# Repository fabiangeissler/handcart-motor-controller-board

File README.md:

# handcart-motor-controller-board
High Power (24V, >1kW) motor controller board for use in electric handcart. Communication via RS-485 bus.

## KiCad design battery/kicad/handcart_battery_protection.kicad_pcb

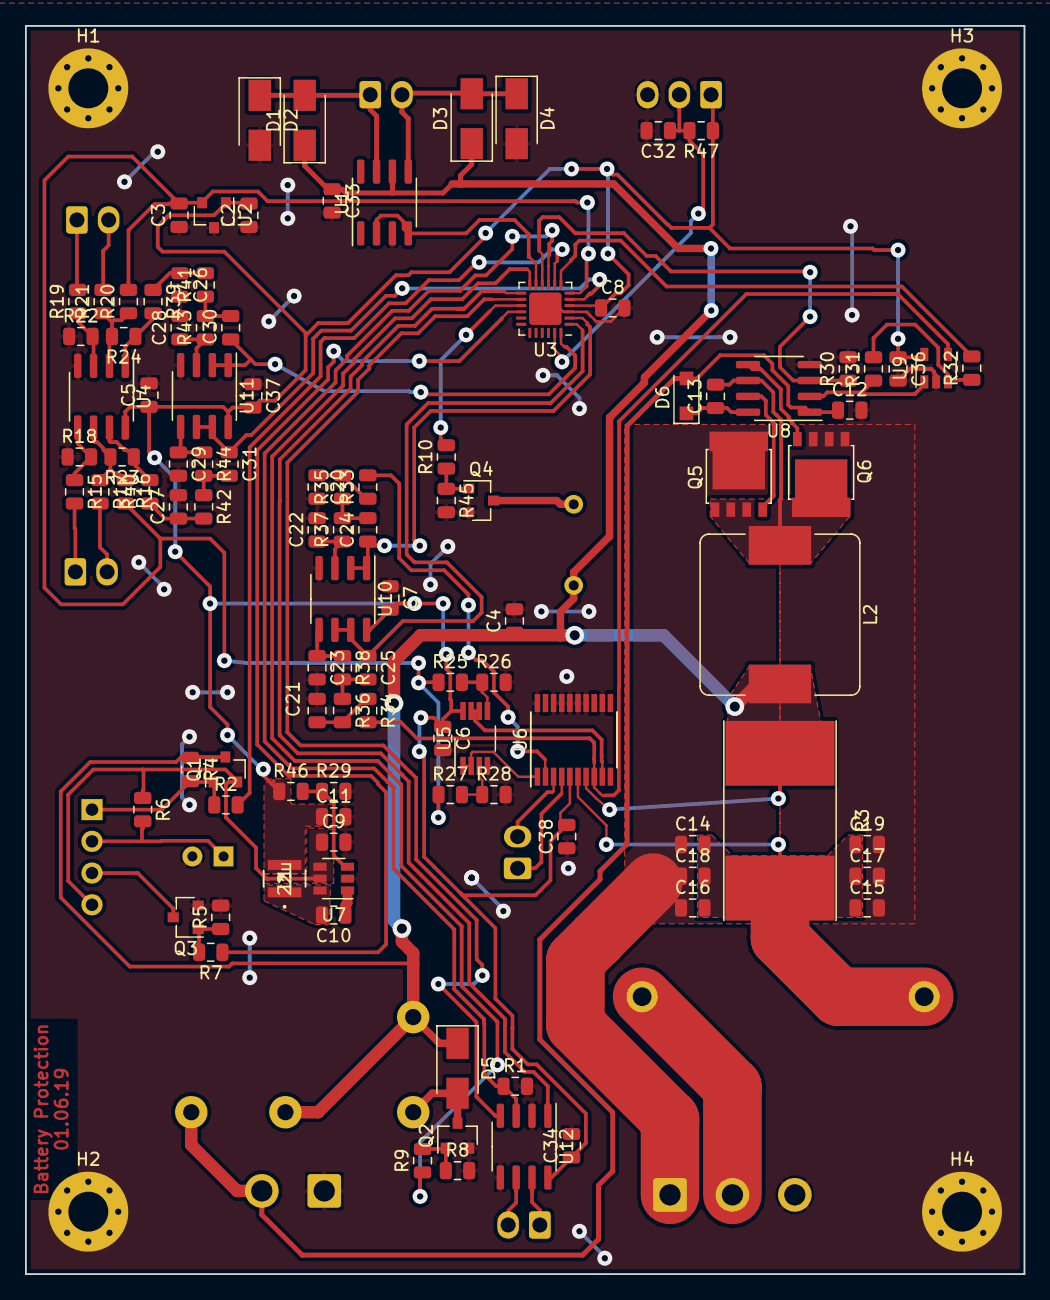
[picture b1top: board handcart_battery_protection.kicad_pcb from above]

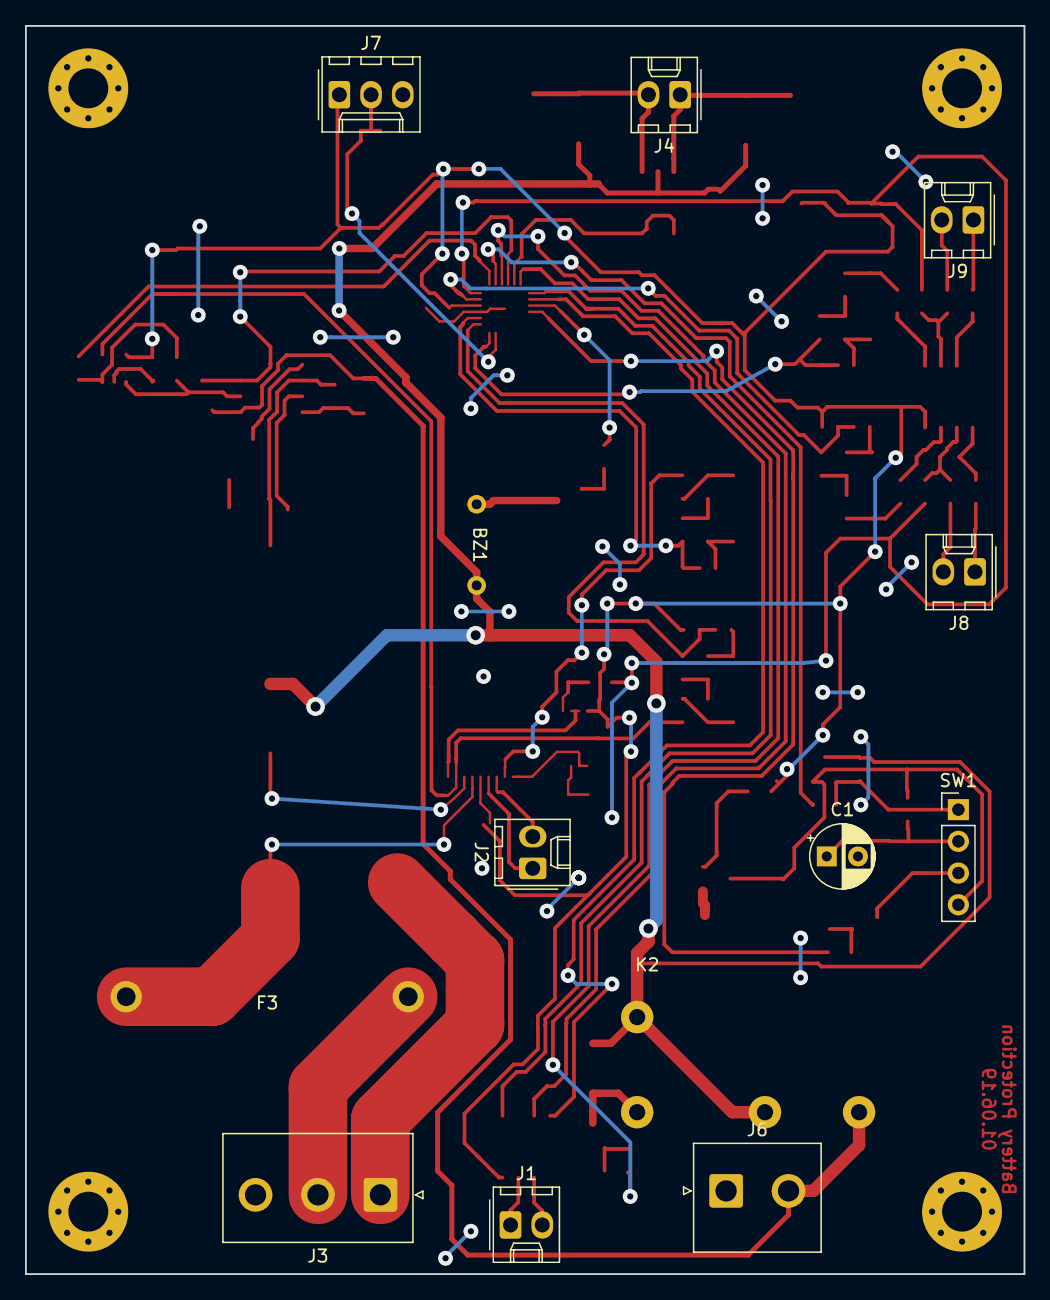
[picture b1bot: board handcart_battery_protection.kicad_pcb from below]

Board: 2 copper layers, 80.0 x 100.0 mm, 122 parts (13 on the bottom side), 74 nets.

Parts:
BZ1: Sound_Alarm_Buzzer; Sound_Buzzer
C1: 100u; CP_Radial_D5.0mm_P2.50mm
C2: 1u; C_0805_2012Metric
C3, C4, C5, C6, C7, C8, C10, C13, C32, C33, C34, C36, C37, C38: 100n; C_0805_2012Metric
C9: 10u/50V; C_0805_2012Metric
C11, C14, C15, C16, C17, C18, C19: 22u/25V; C_0805_2012Metric
C12: 10u/25V; C_0805_2012Metric
C20, C21, C26, C27: 2.2n; C_0805_2012Metric
C22, C23, C28, C29: 150p; C_0805_2012Metric
C24, C25, C30, C31: 1n; C_0805_2012Metric
D1, D2, D3, D4, D5: BAT54-7-F; D_SMA
D6: CRH01(TE85L,Q,M); D_SOD-123F
F3: Fuse 1A, Littelfuse Inc. 39211000000; Fuse_Holder
H1, H2, H3, H4: MountingHole_Pad; MountingHole_3.2mm_M3_Pad_Via
J1: Bus; Molex_KK-254_AE-6410-02A_1x02_P2.54mm_Vertical
J2: 100A_Shunt_In; Molex_KK-254_AE-6410-02A_1x02_P2.54mm_Vertical
J3: Bat_In; JST_NV_B03P-NV_1x03_P5.00mm_Vertical
J4: 100A_Relay_G9TB_Coil; Molex_KK-254_AE-6410-02A_1x02_P2.54mm_Vertical
J6: 12V_Out; JST_NV_B02P-NV_1x02_P5.00mm_Vertical
J7: Program; Molex_KK-254_AE-6410-03A_1x03_P2.54mm_Vertical
J8: BatSense1; Molex_KK-254_AE-6410-02A_1x02_P2.54mm_Vertical
J9: BatSense2; Molex_KK-254_AE-6410-02A_1x02_P2.54mm_Vertical
K2: ALQ3F12
L1: 22u; NR3010T220M
L2: SRP1265A-470M; L_Bourns_SRP1245A
Q1: CMPDM302PH TR; SOT-23
Q2, Q3, Q4: ‎BSS816NWH6327XTSA1‎; SOT-23
Q5, Q6: PSMN013-30YLC; LFPAK
R1, R5, R6, R8, R45: 100k; R_0805_2012Metric
R2, R16, R18, R20, R22, R25, R26, R28, R29, R30: 10k; R_0805_2012Metric
R3: 1m; R_Shunt_WSLP59311
R4: 47k; R_0805_2012Metric
R7, R9, R10: 100; R_0805_2012Metric
R15, R19: 60k; R_0805_2012Metric
R17, R21: 40k; R_0805_2012Metric
R23, R24: 20k; R_0805_2012Metric
R27: 73.3k; R_0805_2012Metric
R31: 180k; R_0805_2012Metric
R32: 6.8k; R_0805_2012Metric
R33, R34, R39, R40: 13k; R_0805_2012Metric
R35, R36, R41, R42: 110k; R_0805_2012Metric
R37, R38, R43, R44: 39k; R_0805_2012Metric
R46: 23.7k; R_0805_2012Metric
R47: 4.7k; R_0805_2012Metric
SW1: SW_Push_LED; PinHeader_1x04_P2.54mm_Vertical
U1: TC4428; SOIC-8_3.9x4.9mm_P1.27mm
U2: REF3025; SOT-23
U3: ATtiny1617-M; QFN-24-1EP_4x4mm_P0.5mm_EP2.6x2.6mm
U4, U10, U11: LMC6482; SOIC-8_3.9x4.9mm_P1.27mm
U5: TLV9062; VSSOP-8_3.0x3.0mm_P0.65mm
U6: INA4181; TSSOP-20_4.4x6.5mm_P0.65mm
U7: TPS560430; SOT-23-6
U8: IRS2008S; SOIC-8_3.9x4.9mm_P1.27mm
U9: TLV3201; SOT-23-5
U12: ST3485; SOIC-8_3.9x4.9mm_P1.27mm

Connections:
+2V5: C3.2, R16.2, R20.2, R25.1, R27.1, U2.2, U3.6
+3V3: C2.2, C5.1, C6.1, C7.2, C8.1, C11.1, C34.1, C36.1, C37.2, C38.2, J7.1, L1.2, R46.1, R47.1, U2.1, U3.4, U4.8, U5.8, U6.5, U9.5, U10.8, U11.8, U12.8
/5A_sense: C25.1, U3.1, U10.6, U10.7
/5A_sense_unfiltered: R34.2, U6.8, U9.4
/12V_Bat: C14.2, C15.1, C16.2, C17.1, C18.2, C19.1, F3.1, R3.2, U6.6
/12V_rail: BZ1.1, C4.1, C33.1, D1.1, D3.1, D5.1, K2.2, K2.3, L2.2, Q1.3, R3.1, R4.1, U1.6, U6.7
/12V_relay_ctrl: R9.1, U3.12
/12V_sense: C31.1, U3.5, U11.6, U11.7
/12V_switchable: C12.1, D6.2, J6.2, K2.4, U8.1
/24V_Bat: C14.1, C16.1, C18.1, J3.1, Q5.3
/24V_relay_ctrl: U1.2, U1.4, U3.11
/24V_sense: C30.1, U3.24, U11.1, U11.2
/100A_sense: C24.1, U3.2, U10.1, U10.2
/100A_sense_H: J2.1, U6.4
/100A_sense_L: F3.2, J2.2, J3.2, U6.3
/BUS_A: J1.2, U12.6
/BUS_B: J1.1, U12.7
/DAC_Balancer_Vset: R32.2, U3.7
/LED: R7.1, U3.16
/TX_EN: R1.1, U3.9, U12.3
/UART_Rx: U3.13, U12.1
/UART_Tx: U3.14, U12.4
/buzzer_pwm: R10.2, U3.15
/current_monitor/0.3V: U5.1, U5.2, U6.1
/current_monitor/100A_sense: R33.2, U6.2
/uC_VDD: C9.1, Q1.2, R6.1, SW1.4, U7.4, U7.5
/voltage_monitor/12V_sense: R23.1, R40.2, U4.7
/voltage_monitor/24V_sense: R24.1, R39.2, U4.1
/~BAL_Shutdown: R30.1, U3.10, U8.3
/~RESET~_UPDI: C32.1, J7.2, R47.2, U3.23
/~uC_EN: R2.2, U3.8
GND: C1.2, C2.1, C3.1, C4.2, C5.2, C6.2, C7.1, C8.2, C9.2, C11.2, C12.2, C15.2, C17.2, C19.2, C20.2, C21.2, C22.2, C23.2, C26.2, C27.2, C28.2, C29.2, C32.2, C33.2, C34.2, C36.2, C37.1, C38.1, D2.2, D4.2, H1.1, H2.1, H3.1, H4.1, J3.3, J6.1, J7.3, Q2.2, Q3.2, Q4.2, Q6.1, R1.2, R5.2, R8.2, R18.1, R22.1, R26.2, R28.2, R29.2, R30.2, R45.2, U1.3, U2.3, U3.3, U3.25, U4.4, U5.4, U6.12, U6.14, U6.15, U6.16, U6.17, U6.18, U6.20, U7.2, U8.4, U9.2, U10.4, U11.4, U12.2, U12.5
unnamed: BZ1.2, Q4.3
unnamed: C1.1, R6.2, SW1.2
unnamed: C10.1, U7.1
unnamed: C10.2, L1.1, U7.6
unnamed: C13.1, D6.1, U8.8
unnamed: C13.2, L2.1, Q5.1, Q6.3, U8.6
unnamed: C20.1, R33.1, R35.2
unnamed: C21.1, R34.1, R36.2
unnamed: C22.1, R37.1, U10.3
unnamed: C23.1, R38.1, U10.5
unnamed: C24.2, R35.1, R37.2
unnamed: C25.2, R36.1, R38.2
unnamed: C26.1, R39.1, R41.2
unnamed: C27.1, R40.1, R42.2
unnamed: C28.1, R43.1, U11.3
unnamed: C29.1, R44.1, U11.5
unnamed: C30.2, R41.1, R43.2
unnamed: C31.2, R42.1, R44.2
unnamed: D1.2, D2.1, J4.1, U1.7
unnamed: D3.2, D4.1, J4.2, U1.5
unnamed: D5.2, K2.1, Q2.3
unnamed: J8.1, R15.2
unnamed: J8.2, R17.2
unnamed: J9.1, R19.2
unnamed: J9.2, R21.2
unnamed: Q1.1, R2.1, R4.2, SW1.1
unnamed: Q2.1, R8.1, R9.2
unnamed: Q3.1, R5.1, R7.2
unnamed: Q3.3, SW1.3
unnamed: Q4.1, R10.1, R45.1
unnamed: Q5.2, U8.7
unnamed: Q6.2, U8.5
unnamed: R15.1, R18.2, U4.5
unnamed: R16.1, R17.1, R23.2, U4.6
unnamed: R19.1, R22.2, U4.3
unnamed: R20.1, R21.1, R24.2, U4.2
unnamed: R25.2, R26.1, U5.5
unnamed: R27.2, R28.1, U5.3
unnamed: R29.1, R46.2, U7.3
unnamed: R31.1, U8.2, U9.1
unnamed: R31.2, R32.1, U9.3
unnamed: U5.6, U5.7, U6.9

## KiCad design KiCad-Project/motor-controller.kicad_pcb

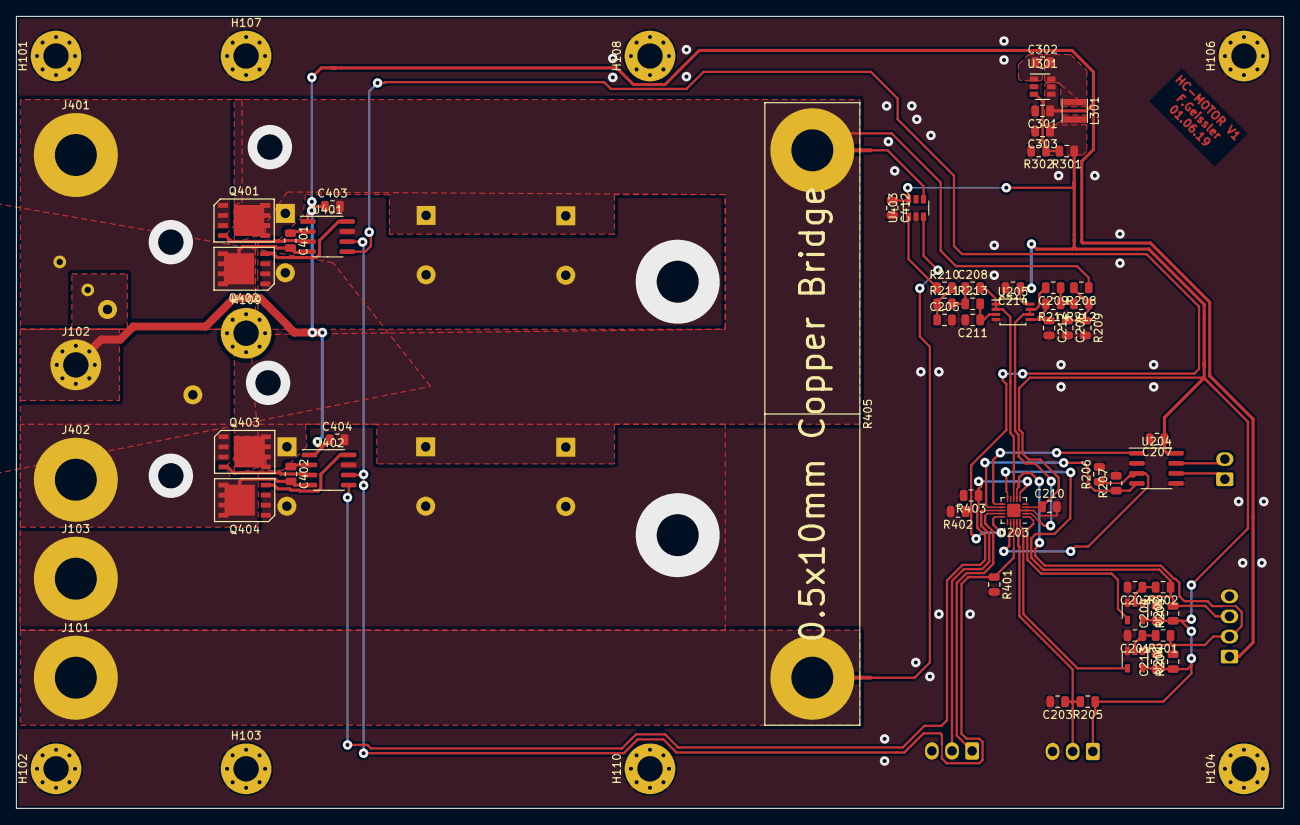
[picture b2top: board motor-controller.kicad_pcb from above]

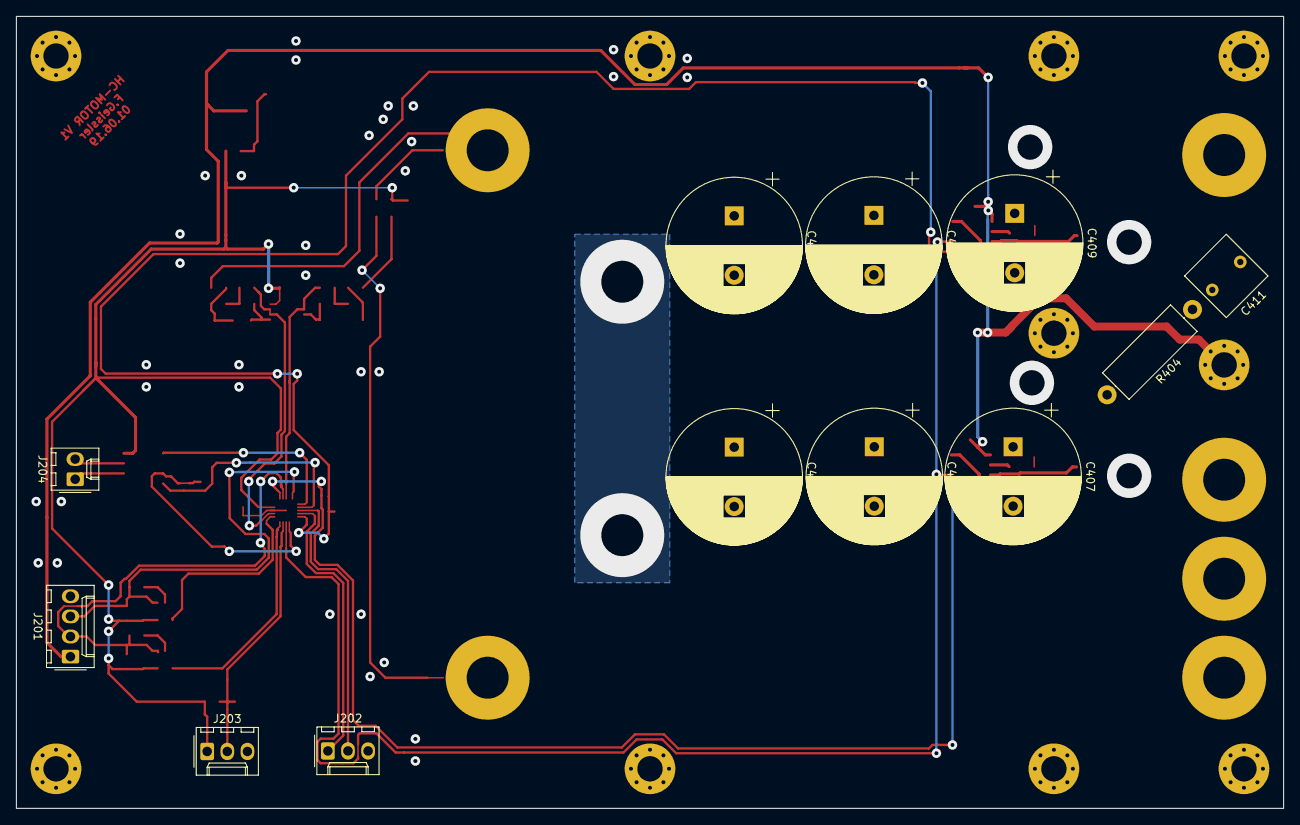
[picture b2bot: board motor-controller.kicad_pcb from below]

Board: 2 copper layers, 160.0 x 100.0 mm, 82 parts (12 on the bottom side), 45 nets.

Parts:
C201, C202: 100p; C_0805_2012Metric
C203, C208, C209: 1n; C_0805_2012Metric
C204, C207, C210, C213, C214, C412: 100n; C_0805_2012Metric
C205, C206: 2n2; C_0805_2012Metric
C211, C212: 150p; C_0805_2012Metric
C301: 10u/50V; C_0805_2012Metric
C302: 100n/C0G; C_0805_2012Metric
C303, C403, C404: 22u/25V; C_0805_2012Metric
C401, C402: 1u/25V; C_0805_2012Metric
C405, C406, C407, C408, C409, C410: 1000u/63V/Low ESR; CP_Radial_D17.0mm_P7.50mm
C411: 47n; C_Rect_L7.2mm_W7.2mm_P5.00mm_FKS2_FKP2_MKS2_MKP2
H101, H102, H104, H106, H108, H110: GND; MountingHole_3.2mm_M3_Pad_Via
H103, H107, H109: HS; MountingHole_3.2mm_M3_Pad_Via
J101: 24V; MountingHole_5.3mm_M5_Pad
J102: 12V; MountingHole_3.2mm_M3_Pad_Via
J103: GND; MountingHole_5.3mm_M5_Pad
J201: Encoder; Molex_KK-254_AE-6410-04A_1x04_P2.54mm_Vertical
J202: GPIO; Molex_KK-254_AE-6410-03A_1x03_P2.54mm_Vertical
J203: UPDI; Molex_KK-254_AE-6410-03A_1x03_P2.54mm_Vertical
J204: Bus; Molex_KK-254_AE-6410-02A_1x02_P2.54mm_Vertical
J401: MOTOR; MountingHole_5.3mm_M5_Pad
J402: ~MOTOR; MountingHole_5.3mm_M5_Pad
L301: NR3010T220M; L_Taiyo-Yuden_NR-30xx
Q401, Q402, Q403, Q404: DMTH6002LPS; PowerDI5060-8_SGD
R201, R202: 100k; R_0805_2012Metric
R203, R204, R205: 4k7; R_0805_2012Metric
R206, R207, R401, R402, R403: 47k; R_0805_2012Metric
R208: 390k; R_0805_2012Metric
R209: 14k; R_0805_2012Metric
R210: 13k; R_0805_2012Metric
R211, R212: 110k; R_0805_2012Metric
R213, R214: 39k; R_0805_2012Metric
R301: 62k; R_0805_2012Metric
R302: 27k; R_0805_2012Metric
R404: 0R75; R_Axial_DIN0414_L11.9mm_D4.5mm_P15.24mm_Horizontal
R405: 200uR; PCB_Shunt_200uR
U201, U202: SN74AHC1G86; SOT-23-5
U203: ATtiny416-M; VQFN-20-1EP_3x3mm_P0.4mm_EP1.7x1.7mm
U204: ST3485; SOIC-8_3.9x4.9mm_P1.27mm
U205: TLV9062; TSSOP-8_3x3mm_P0.65mm
U301: TPS560430Y; SOT-23-6
U401, U402: MIC4102; SOIC-8_3.9x4.9mm_P1.27mm
U403: LMP8640-H; SOT-23-6

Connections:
+3V3: C204.1, C207.1, C210.1, C213.1, C214.1, C303.1, C412.1, J203.1, L301.2, R203.1, R204.1, R205.1, R301.1, U201.5, U202.5, U203.4, U204.8, U205.8, U403.6
+12V: C301.1, C403.1, C404.1, J102.1, J201.1, U301.4, U301.5, U401.1, U402.1
+24V: J101.1, R405.1
/Controller/ADC_CURRENT: C208.2, U203.8, U205.1, U205.2
/Controller/ADC_VOLTAGE: C209.2, U203.2, U205.6, U205.7
/Controller/BR_CURRENT: R210.1, U403.1
/Controller/BR_EN: R401.1, U203.18, U401.6, U402.6
/Controller/GPIO_B0: J202.1, U203.14
/Controller/GPIO_B1: J202.2, U203.13
/Controller/PWM: R402.1, U203.15, U401.5
/Controller/ROT_A: J201.2, R201.1, R204.2, U201.1, U203.7
/Controller/ROT_A_EDGE: U201.4, U203.20
/Controller/ROT_B: J201.3, R202.1, R203.2, U202.1, U203.10
/Controller/ROT_B_EDGE: U202.4, U203.1
/Controller/RXD: U203.11, U204.1
/Controller/TXD: R207.1, U203.12, U204.4
/Controller/TX_EN: R206.1, U203.17, U204.3
/Controller/VRAIL: C405.1, C406.1, C407.1, C408.1, C409.1, C410.1, Q401.3, Q403.3, R208.1, R405.4
/Controller/~PWM: R403.1, U203.6, U402.5
/Controller/~RESET: C203.1, J203.2, R205.2, U203.19
GND: C201.2, C202.2, C203.2, C204.2, C205.2, C206.2, C207.2, C210.2, C211.2, C212.2, C213.2, C214.2, C301.2, C303.2, C403.2, C404.2, C405.2, C406.2, C407.2, C408.2, C409.2, C410.2, C412.2, H101.1, H102.1, H103.1, H104.1, H106.1, H107.1, H108.1, H109.1, H110.1, J103.1, J201.4, J202.3, J203.3, Q402.1, Q404.1, R206.2, R207.2, R209.2, R302.2, R401.2, R402.2, R403.2, U201.3, U202.3, U203.3, U203.21, U204.2, U204.5, U205.4, U301.2, U401.7, U402.7, U403.2
unnamed: C201.1, R201.2, U201.2
unnamed: C202.1, R202.2, U202.2
unnamed: C205.1, R210.2, R211.1
unnamed: C206.1, R208.2, R209.1, R212.1
unnamed: C208.1, R211.2, R213.1
unnamed: C209.1, R212.2, R214.1
unnamed: C211.1, R213.2, U205.3
unnamed: C212.1, R214.2, U205.5
unnamed: C302.1, U301.1
unnamed: C302.2, L301.1, U301.6
unnamed: C401.1, U401.2
unnamed: C401.2, C411.1, J401.1, Q401.1, Q402.3, U401.4
unnamed: C402.1, U402.2
unnamed: C402.2, J402.1, Q403.1, Q404.3, R404.2, U402.4
unnamed: C411.2, R404.1
unnamed: J204.1, U204.6
unnamed: J204.2, U204.7
unnamed: Q401.2, U401.3
unnamed: Q402.2, U401.8
unnamed: Q403.2, U402.3
unnamed: Q404.2, U402.8
unnamed: R301.2, R302.1, U301.3
unnamed: R405.2, U403.3
unnamed: R405.3, U403.4

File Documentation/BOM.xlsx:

Reference | Value | Footprint | Quantity
C201 | 100p | Capacitor_SMD:C_0805_2012Metric | 1
C202 | 100p | Capacitor_SMD:C_0805_2012Metric | 1
C203 | 1n | Capacitor_SMD:C_0805_2012Metric | 1
C204 | 100n | Capacitor_SMD:C_0805_2012Metric | 1
C205 | 2n2 | Capacitor_SMD:C_0805_2012Metric | 1
C206 | 2n2 | Capacitor_SMD:C_0805_2012Metric | 1
C207 | 100n | Capacitor_SMD:C_0805_2012Metric | 1
C208 | 1n | Capacitor_SMD:C_0805_2012Metric | 1
C209 | 1n | Capacitor_SMD:C_0805_2012Metric | 1
C210 | 100n | Capacitor_SMD:C_0805_2012Metric | 1
C211 | 150p | Capacitor_SMD:C_0805_2012Metric | 1
C212 | 150p | Capacitor_SMD:C_0805_2012Metric | 1
C213 | 100n | Capacitor_SMD:C_0805_2012Metric | 1
C214 | 100n | Capacitor_SMD:C_0805_2012Metric | 1
C301 | 10u/50V | Capacitor_SMD:C_1206_3216Metric | 1
C302 | 100n/C0G | Capacitor_SMD:C_0805_2012Metric | 1
C303 | 22u/25V | Capacitor_SMD:C_1206_3216Metric | 1
C401 | 1u/25V | Capacitor_SMD:C_0805_2012Metric | 1
C402 | 1u/25V | Capacitor_SMD:C_0805_2012Metric | 1
C403 | 22u/25V | Capacitor_SMD:C_1206_3216Metric | 1
C404 | 22u/25V | Capacitor_SMD:C_1206_3216Metric | 1
C405 | 1000u/63V/Low ESR | Capacitor_THT:CP_Radial_D17.0mm_P7.50mm | 1
C406 | 1000u/63V/Low ESR | Capacitor_THT:CP_Radial_D17.0mm_P7.50mm | 1
C407 | 1000u/63V/Low ESR | Capacitor_THT:CP_Radial_D17.0mm_P7.50mm | 1
C408 | 1000u/63V/Low ESR | Capacitor_THT:CP_Radial_D17.0mm_P7.50mm | 1
C409 | 1000u/63V/Low ESR | Capacitor_THT:CP_Radial_D17.0mm_P7.50mm | 1
C410 | 1000u/63V/Low ESR | Capacitor_THT:CP_Radial_D17.0mm_P7.50mm | 1
C411 | 47n | Capacitor_THT:C_Rect_L7.2mm_W7.2mm_P5.00mm_FKS2_FKP2_MKS2_MKP2 | 1
C412 | 100n | Capacitor_SMD:C_0805_2012Metric | 1
H101 | GND | MountingHole:MountingHole_3.2mm_M3_Pad_Via | 1
H102 | GND | MountingHole:MountingHole_3.2mm_M3_Pad_Via | 1
H103 | HS | MountingHole:MountingHole_3.2mm_M3_Pad_Via | 1
H104 | GND | MountingHole:MountingHole_3.2mm_M3_Pad_Via | 1
H105 | HS | MountingHole:MountingHole_3.2mm_M3_Pad_Via | 1
H106 | GND | MountingHole:MountingHole_3.2mm_M3_Pad_Via | 1
H107 | HS | MountingHole:MountingHole_3.2mm_M3_Pad_Via | 1
H108 | GND | MountingHole:MountingHole_3.2mm_M3_Pad_Via | 1
H109 | HS | MountingHole:MountingHole_3.2mm_M3_Pad_Via | 1
H110 | GND | MountingHole:MountingHole_3.2mm_M3_Pad_Via | 1
J101 | 24V | MountingHole:MountingHole_5.3mm_M5_Pad | 1
J102 | 12V | MountingHole:MountingHole_3.2mm_M3_Pad_Via | 1
J103 | GND | MountingHole:MountingHole_5.3mm_M5_Pad | 1
J201 | Encoder | Connector_Molex:Molex_KK-254_AE-6410-04A_1x04_P2.54mm_Vertical | 1
J202 | GPIO | Connector_Molex:Molex_KK-254_AE-6410-03A_1x03_P2.54mm_Vertical | 1
J203 | UPDI | Connector_Molex:Molex_KK-254_AE-6410-02A_1x02_P2.54mm_Vertical | 1
J204 | Bus | Connector_Molex:Molex_KK-254_AE-6410-02A_1x02_P2.54mm_Vertical | 1
J401 | MOTOR | MountingHole:MountingHole_5.3mm_M5_Pad | 1
J402 | ~MOTOR | MountingHole:MountingHole_5.3mm_M5_Pad | 1
L301 | NR3010T220M | Inductor_SMD:L_Taiyo-Yuden_NR-30xx | 1
Q401 | DMTH6002LPS | handcart-footprints:PowerDI5060-8_SGD | 1
Q402 | DMTH6002LPS | handcart-footprints:PowerDI5060-8_SGD | 1
Q403 | DMTH6002LPS | handcart-footprints:PowerDI5060-8_SGD | 1
Q404 | DMTH6002LPS | handcart-footprints:PowerDI5060-8_SGD | 1
R201 | 100k | Resistor_SMD:R_0805_2012Metric | 1
R202 | 100k | Resistor_SMD:R_0805_2012Metric | 1
R203 | 4k7 | Resistor_SMD:R_0805_2012Metric | 1
R204 | 4k7 | Resistor_SMD:R_0805_2012Metric | 1
R205 | 4k7 | Resistor_SMD:R_0805_2012Metric | 1
R206 | 47k | Resistor_SMD:R_0805_2012Metric | 1
R207 | 47k | Resistor_SMD:R_0805_2012Metric | 1
R208 | 390k | Resistor_SMD:R_0805_2012Metric | 1
R209 | 14k | Resistor_SMD:R_0805_2012Metric | 1
R210 | 13k | Resistor_SMD:R_0805_2012Metric | 1
R211 | 110k | Resistor_SMD:R_0805_2012Metric | 1
R212 | 110k | Resistor_SMD:R_0805_2012Metric | 1
R213 | 39k | Resistor_SMD:R_0805_2012Metric | 1
R214 | 39k | Resistor_SMD:R_0805_2012Metric | 1
R301 | 62k | Resistor_SMD:R_0805_2012Metric | 1
R302 | 27k | Resistor_SMD:R_0805_2012Metric | 1
R401 | 47k | Resistor_SMD:R_0805_2012Metric | 1
R402 | 47k | Resistor_SMD:R_0805_2012Metric | 1
R403 | 47k | Resistor_SMD:R_0805_2012Metric | 1
R404 | 0R75 | Resistor_THT:R_Axial_DIN0414_L11.9mm_D4.5mm_P15.24mm_Horizontal | 1
R405 | 200uR | handcart-footprints:PCB_Shunt_200uR | 1
TP201 | ROT_DIR | TestPoint:TestPoint_Pad_D2.0mm | 1
TP202 | CLK_OUT | TestPoint:TestPoint_Pad_D2.0mm | 1
TP203 | ROT_CNT | TestPoint:TestPoint_Pad_D2.0mm | 1
U201 | SN74AHC1G86 | Package_TO_SOT_SMD:SOT-23-5 | 1
U202 | SN74AHC1G86 | Package_TO_SOT_SMD:SOT-23-5 | 1
U203 | ATtiny416-M | Package_DFN_QFN:VQFN-20-1EP_3x3mm_P0.4mm_EP1.7x1.7mm | 1
U204 | ST3485 | Package_SO:SOIC-8_3.9x4.9mm_P1.27mm | 1
U205 | TLV9062 | Package_SO:TSSOP-8_3x3mm_P0.65mm | 1
U301 | TPS560430Y | Package_TO_SOT_SMD:SOT-23-6 | 1
U401 | MIC4102 | Package_SO:SOIC-8_3.9x4.9mm_P1.27mm | 1
U402 | MIC4102 | Package_SO:SOIC-8_3.9x4.9mm_P1.27mm | 1
U403 | LMP8640-H | Package_TO_SOT_SMD:SOT-23-6 | 1

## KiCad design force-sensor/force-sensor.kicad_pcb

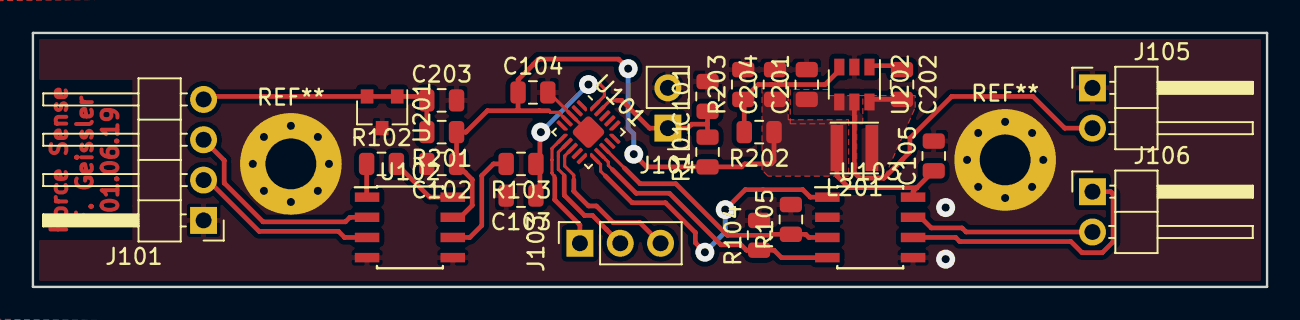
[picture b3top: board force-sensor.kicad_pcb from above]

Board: 2 copper layers, 77.8 x 16.0 mm, 28 parts (0 on the bottom side), 22 nets.

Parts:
C101: 1n; C_0805_2012Metric
C102, C104, C105: 100n; C_0805_2012Metric
C103, C203: 1u; C_0805_2012Metric
C201: 10u/50V; C_0805_2012Metric
C202: 100n/C0G; C_0805_2012Metric
C204: 22u/25V; C_0805_2012Metric
J101: Sensor Bridge; PinHeader_1x04_P2.54mm_Horizontal
J103: PA2; PinSocket_1x03_P2.54mm_Vertical
J104: UPDI; PinHeader_1x02_P2.54mm_Vertical
J105: Supply; PinHeader_1x02_P2.54mm_Horizontal
J106: Bus; PinHeader_1x02_P2.54mm_Horizontal
L201: NR3010T220M; L_Taiyo-Yuden_NR-30xx
R101: 10k; R_0805_2012Metric
R102: 33; R_0805_2012Metric
R103: 100; R_0805_2012Metric
R104, R105: 47k; R_0805_2012Metric
R201: 1k; R_0805_2012Metric
R202: 62k; R_0805_2012Metric
R203: 27k; R_0805_2012Metric
U101: ATtiny416-M; VQFN-20-1EP_3x3mm_P0.45mm_EP1.55x1.55mm
U102: INA128; SOIC-8_3.9x4.9mm_P1.27mm
U103: ST3485; SOIC-8_3.9x4.9mm_P1.27mm
U201: TL431DBZ; SOT-23
U202: TPS560430Y; SOT-23-6

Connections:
+2V5: C203.1, J101.4, R201.2, U201.1, U201.2
+3V3: C102.1, C104.1, C105.1, C204.1, L201.2, R101.1, R201.1, R202.1, U101.4, U102.7, U103.8
+12V: C201.1, J105.2, U202.4, U202.5
/RXD: U101.11, U103.1
/TXD: R104.1, U101.12, U103.4
/TX_EN: R105.1, U101.13, U103.3
/VF: C103.1, R103.1, U101.20
GND: C101.2, C102.2, C103.2, C104.2, C105.2, C201.2, C203.2, C204.2, J101.1, J104.2, J105.1, R104.2, R105.2, R203.2, U101.3, U101.21, U102.4, U102.5, U103.2, U103.5, U201.3, U202.2
unnamed: C101.1, J104.1, R101.2, U101.19
unnamed: C202.1, U202.1
unnamed: C202.2, L201.1, U202.6
unnamed: J101.2, U102.3
unnamed: J101.3, U102.2
unnamed: J103.1, U101.6
unnamed: J103.2, U101.7
unnamed: J103.3, U101.8
unnamed: J106.1, U103.6
unnamed: J106.2, U103.7
unnamed: R102.1, U102.1
unnamed: R102.2, U102.8
unnamed: R103.2, U102.6
unnamed: R202.2, R203.1, U202.3

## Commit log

2019-04-26 First version schematic commit.
2019-04-26 Reordered some files.
2019-05-05 Larger controller, included some on-board GPIOs and header for encoder. No 12V buck converter, using 12V single battery supply instead.
2019-05-05 Yet another new controller to perform rotary encoder decoding mostly in hardware.
2019-05-05 Buck converter now uses 12V supply to increase efficiency.
2019-05-30 layout finished
2019-05-31 Single layer Board
2019-05-31 cleanup
2019-05-31 Force sensor modifications
2019-05-31 Foce Sensor Layout
2019-06-01 Battry Protection added
2019-06-01 battery protection

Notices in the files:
parts and their libraries:
Copyright 2016 Accelerated Designs. All rights reserved.
